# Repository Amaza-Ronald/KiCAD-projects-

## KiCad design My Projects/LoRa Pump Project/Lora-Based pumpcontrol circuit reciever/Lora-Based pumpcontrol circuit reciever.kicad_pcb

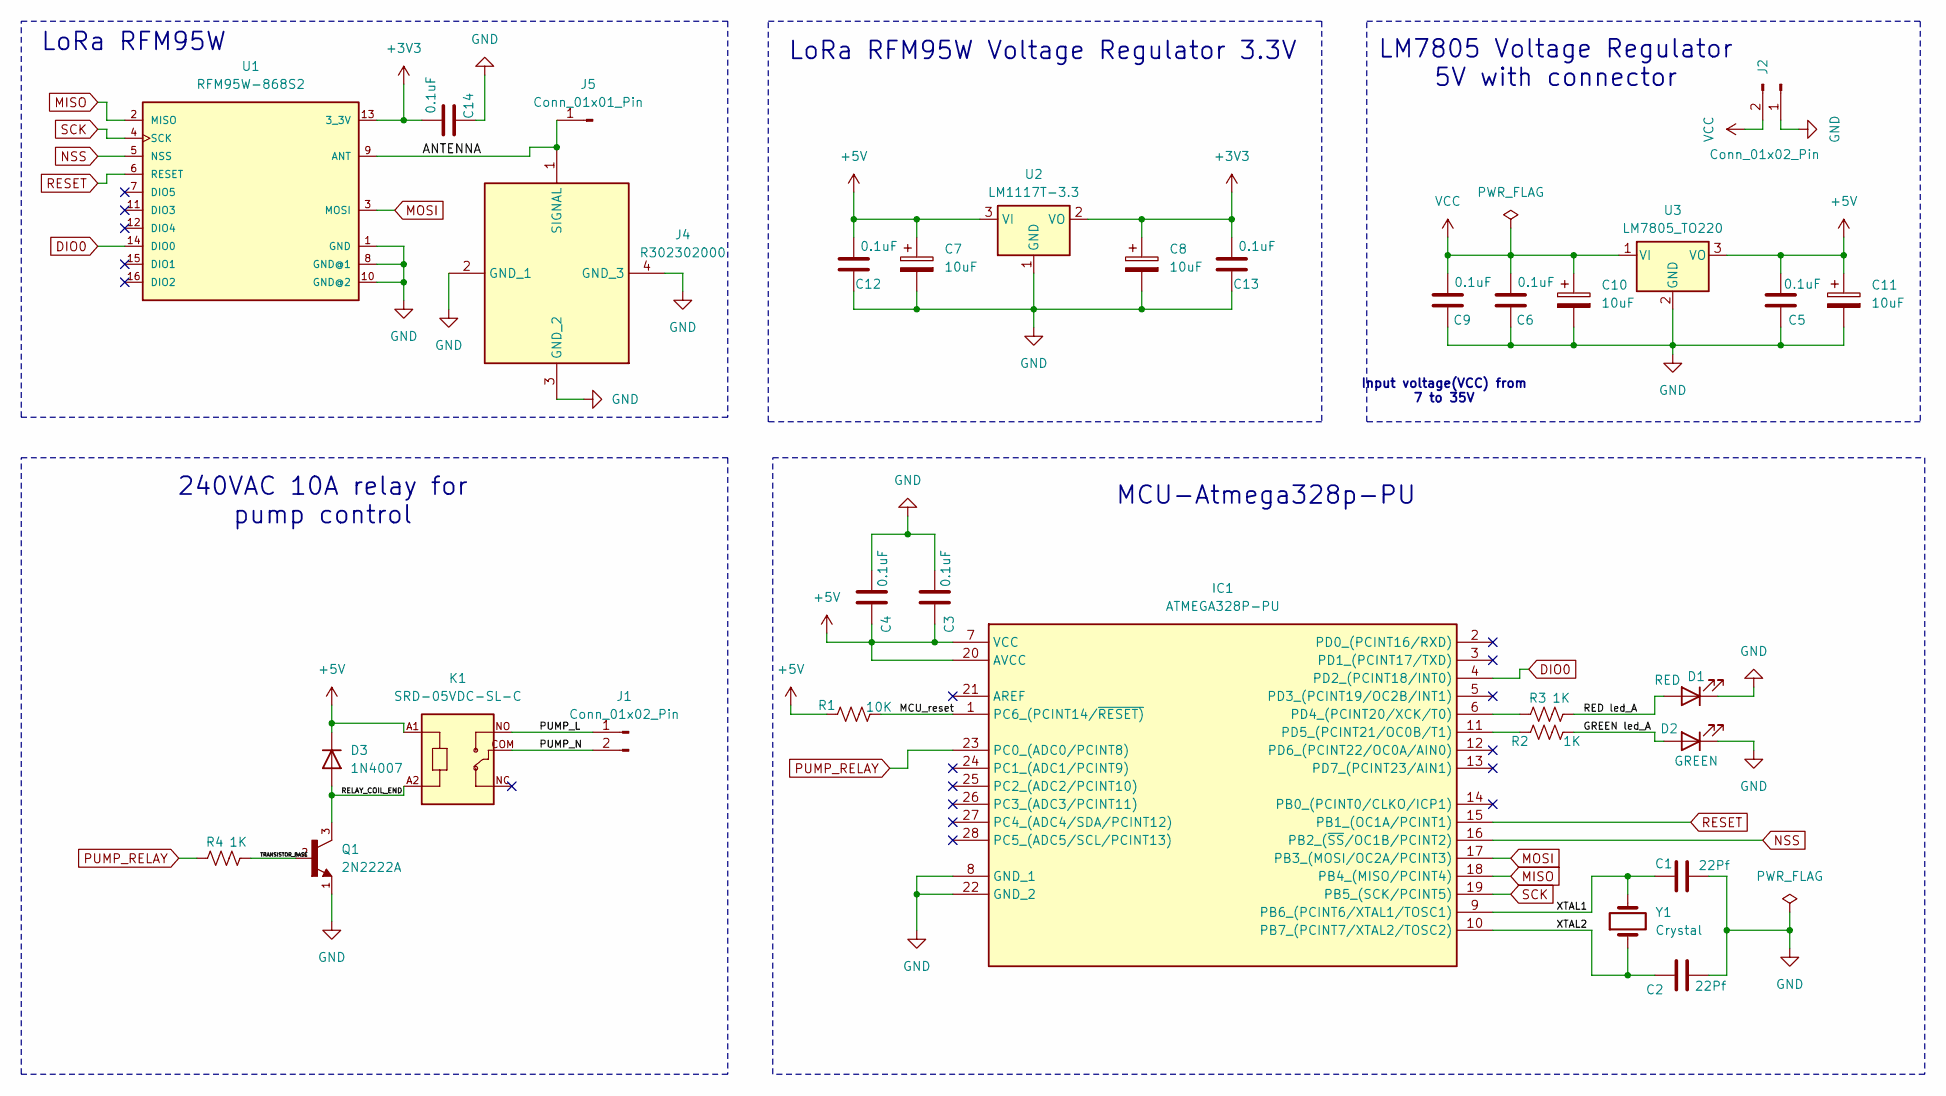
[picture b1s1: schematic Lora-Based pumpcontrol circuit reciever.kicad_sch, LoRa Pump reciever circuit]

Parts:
C1, C2: 22Pf; C_Disc_D3.0mm_W1.6mm_P2.50mm
C3, C4, C5, C6, C9, C12, C13, C14: 0.1uF; C_Disc_D4.3mm_W1.9mm_P5.00mm
C7, C8, C10, C11: 10uF; CP_Radial_D4.0mm_P1.50mm
D1: RED; LED_D3.0mm
D2: GREEN; LED_D3.0mm
D3: 1N4007; D_DO-41_SOD81_P10.16mm_Horizontal
IC1: ATMEGA328P-PU; DIP794W53P254L3467H457Q28N; Manufacturer_Part_Number ATMEGA328P-PU
J1, J2: Conn_01x02_Pin; PhoenixContact_MCV_1,5_2-G-5.08_1x02_P5.08mm_Vertical
J4: R302302000; Mouser Part Number 501-R302302000
J5: Conn_01x01_Pin; PinHeader_1x01_P2.54mm_Vertical
K1: SRD-05VDC-SL-C; RELAY_SRD-05VDC-SL-C
Q1: 2N2222A; TO92254P470H750-3; PARTREV N/A; DigiKey_Part_Number 5245-2N2222A-ND
R1: 10K; R_Axial_DIN0204_L3.6mm_D1.6mm_P5.08mm_Horizontal
R2, R3, R4: 1K; R_Axial_DIN0204_L3.6mm_D1.6mm_P5.08mm_Horizontal
U1: RFM95W-868S2; XCVR_RFM95W-868S2
U2: LM1117T-3.3; TO-220-3_Horizontal_TabDown
U3: LM7805_TO220; TO-220-3_Horizontal_TabDown
Y1: Crystal; Crystal_HC49-4H_Vertical

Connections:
+3V3: C8.1, C13.2, C14.2, U1.13 (3_3V), U2.2 (VO)
+5V: C3.1, C4.1, C5.2, C7.1, C11.1, C12.2, D3.1 (K), IC1.7 (VCC), IC1.20 (AVCC), K1.A1, R1.1, U2.3 (VI), U3.3 (VO)
/ANTENNA: J4.1 (SIGNAL), J5.1, U1.9 (ANT)
/GREEN led_A: D2.2 (A), R2.2
/MCU_reset: IC1.1 (PC6_(PCINT14/~RESET)), R1.2
/PUMP_L: J1.1, K1.NO
/PUMP_N: J1.2, K1.COM
/RED led_A: D1.2 (A), R3.2
/RELAY_COIL_END: D3.2 (A), K1.A2, Q1.3
/TRANSISTOR_BASE: Q1.2, R4.2
/XTAL1: C1.1, IC1.9 (PB6_(PCINT6/XTAL1/TOSC1)), Y1.2
/XTAL2: C2.1, IC1.10 (PB7_(PCINT7/XTAL2/TOSC2)), Y1.1
DIO0: IC1.4 (PD2_(PCINT18/INT0)), U1.14 (DIO0)
GND: C1.2, C2.2, C3.2, C4.2, C5.1, C6.1, C7.2, C8.2, C9.1, C10.2, C11.2, C12.1, C13.1, C14.1, D1.1 (K), D2.1 (K), IC1.8 (GND_1), IC1.22 (GND_2), J2.1, J4.2 (GND_1), J4.3 (GND_2), J4.4 (GND_3), Q1.1, U1.1 (GND), U1.8 (GND@1), U1.10 (GND@2), U2.1 (GND), U3.2 (GND)
MISO: IC1.18 (PB4_(MISO/PCINT4)), U1.2 (MISO)
MOSI: IC1.17 (PB3_(MOSI/OC2A/PCINT3)), U1.3 (MOSI)
NSS: IC1.16 (PB2_(~SS/OC1B/PCINT2)), U1.5 (NSS)
unnamed: IC1.6 (PD4_(PCINT20/XCK/T0)), R3.1
unnamed: IC1.11 (PD5_(PCINT21/OC0B/T1)), R2.1
PUMP_RELAY: IC1.23 (PC0_(ADC0/PCINT8)), R4.1
RESET: IC1.15 (PB1_(OC1A/PCINT1)), U1.6 (RESET)
SCK: IC1.19 (PB5_(SCK/PCINT5)), U1.4 (SCK)
VCC: C6.2, C9.2, C10.1, J2.2, U3.1 (VI)

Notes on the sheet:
LoRa RFM95W Voltage Regulator 3.3V
LM7805 Voltage Regulator 5V with connector
Input voltage(VCC) from 7 to 35V
LoRa RFM95W
MCU-Atmega328p-PU
240VAC 10A relay for pump control

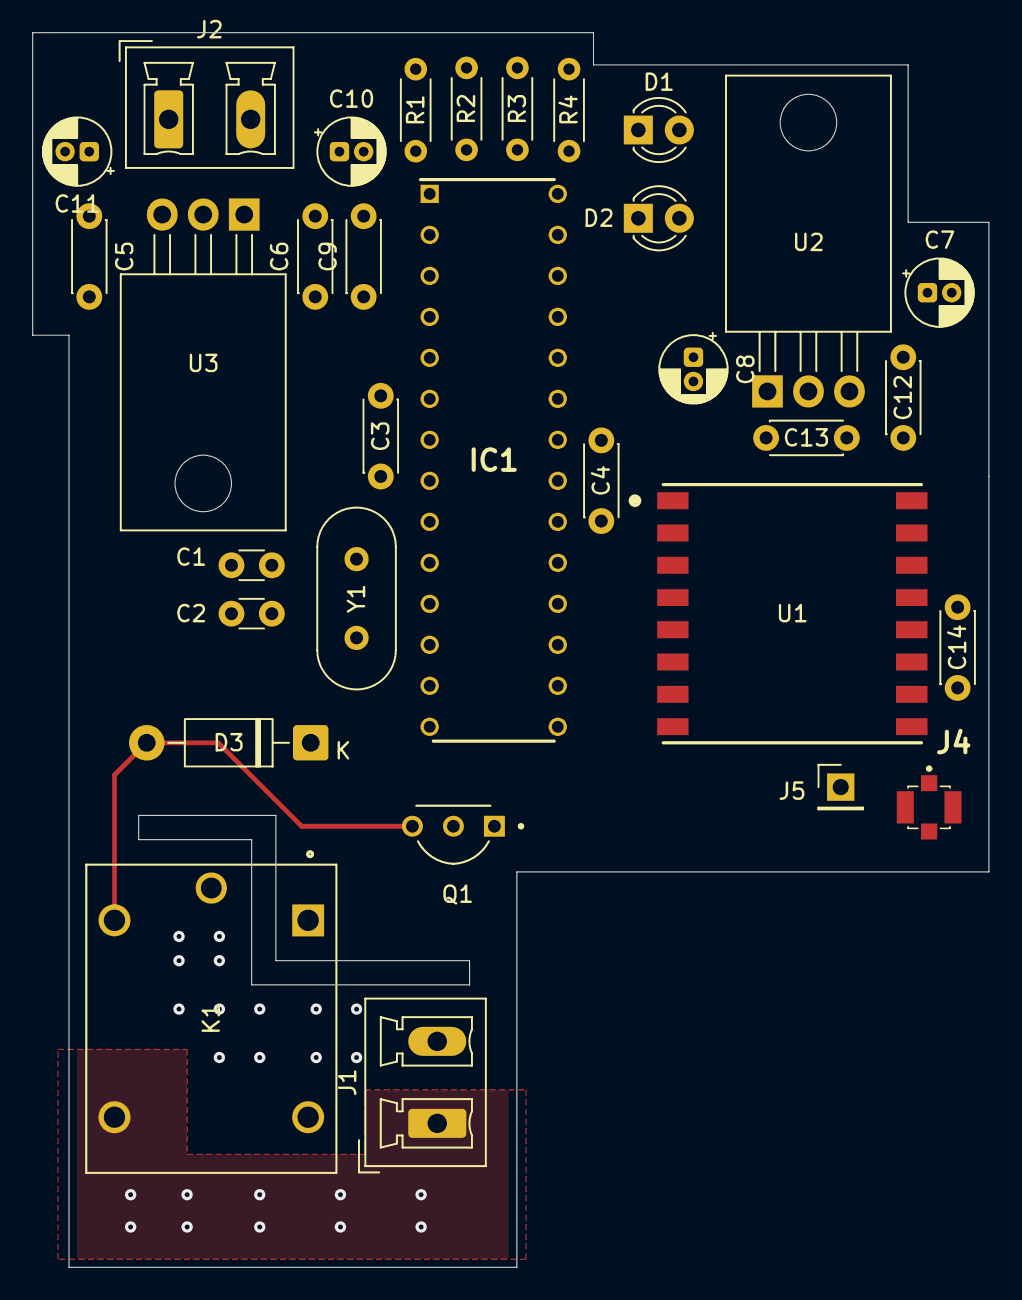
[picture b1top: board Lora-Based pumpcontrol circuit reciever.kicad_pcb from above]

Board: 2 copper layers, 59.2 x 76.5 mm, 32 parts (0 on the bottom side), 23 nets.

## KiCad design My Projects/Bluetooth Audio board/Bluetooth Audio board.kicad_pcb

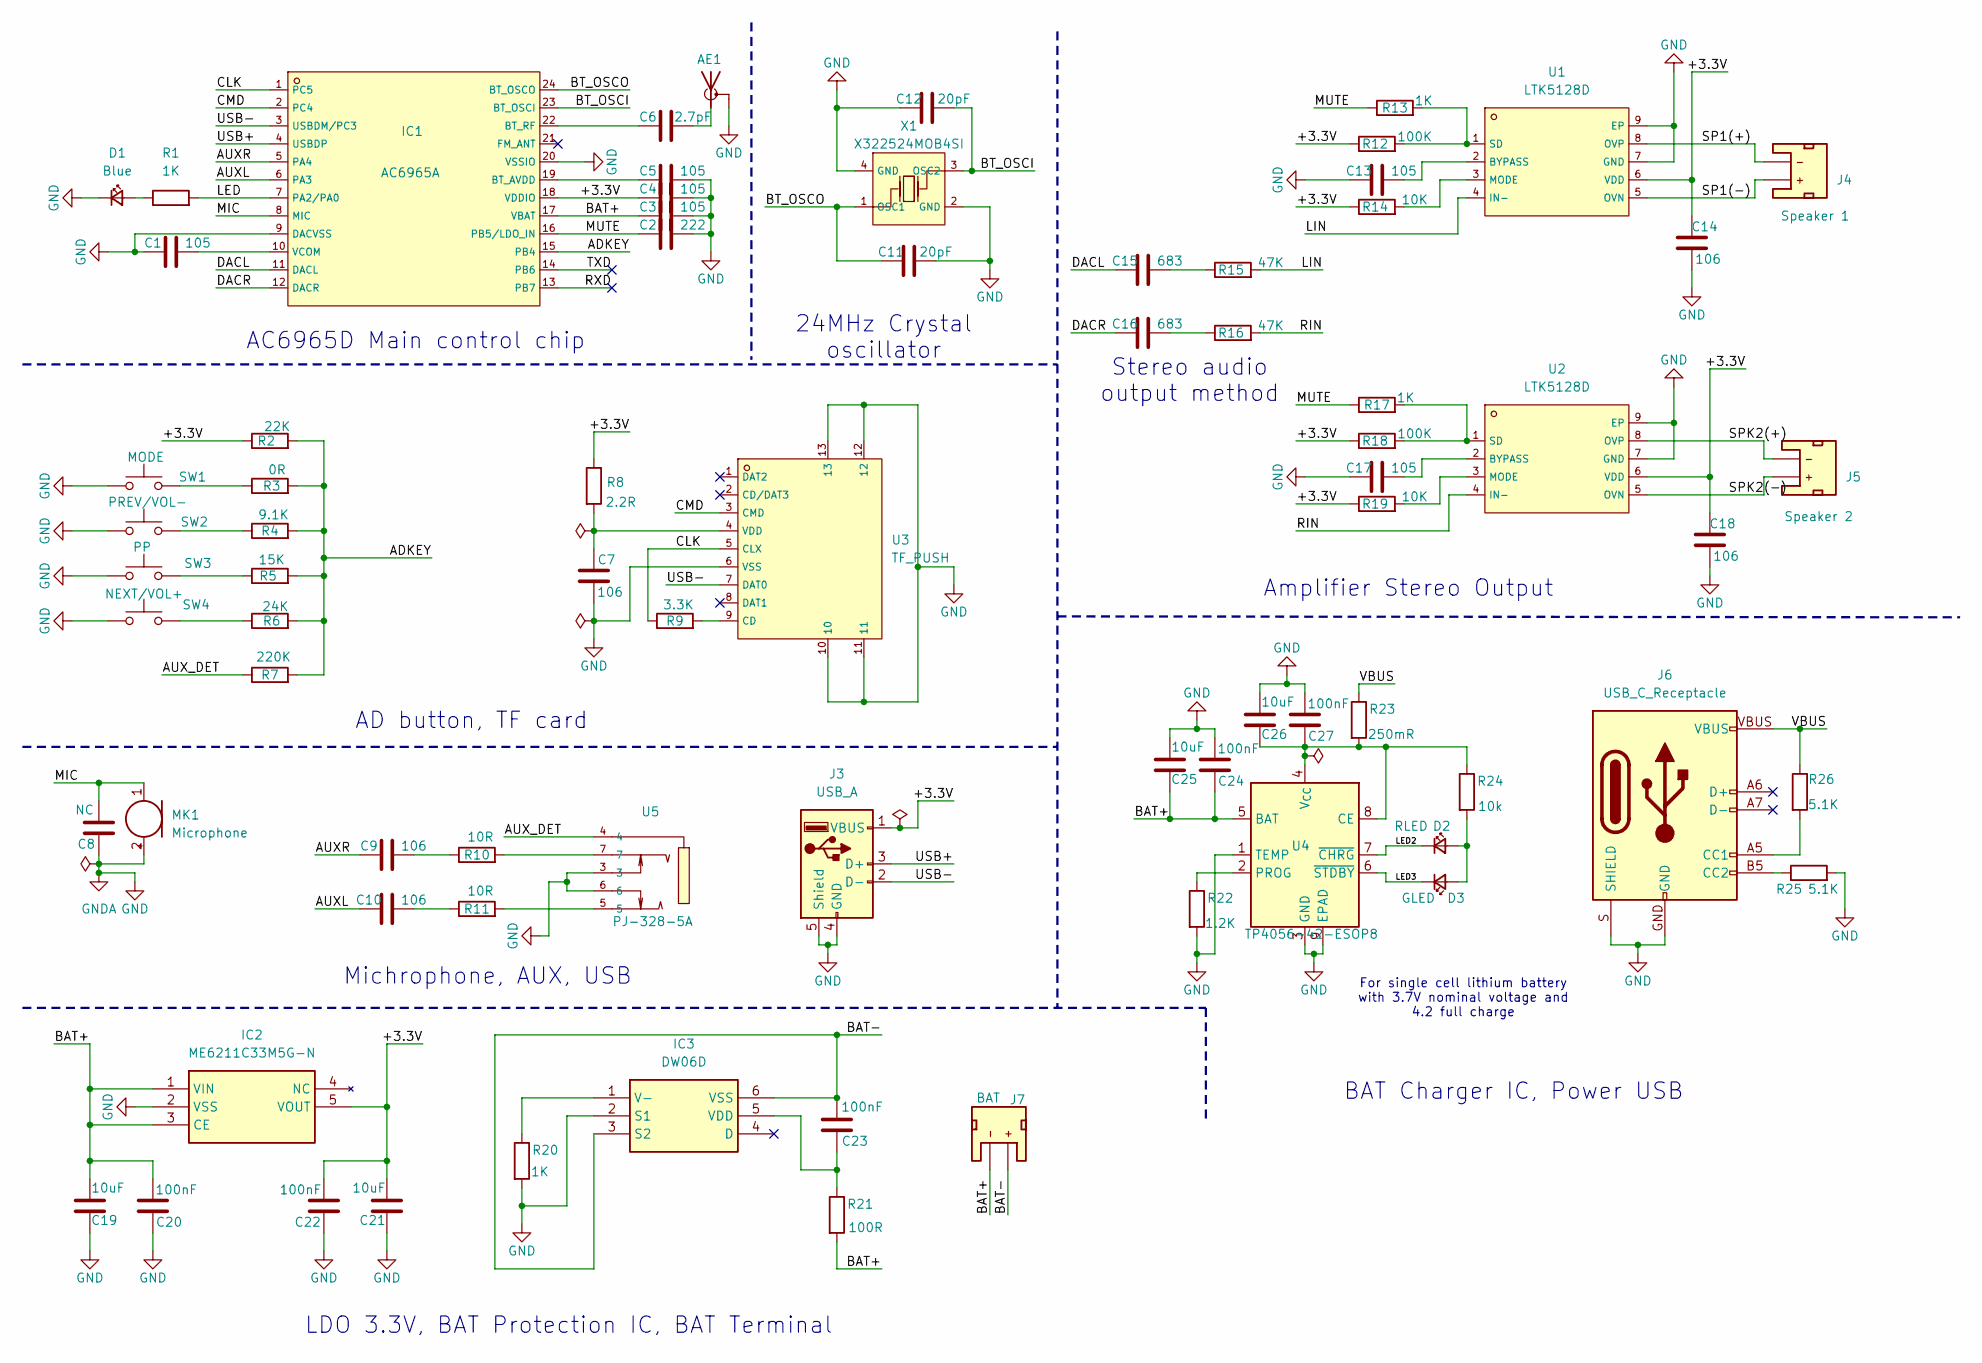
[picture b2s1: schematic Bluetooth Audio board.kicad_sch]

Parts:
AE1: Antenna; Texas_SWRA117D_2.4GHz_Left
C1, C3, C4, C5, C13, C17: 105; C_0603_1608Metric
C2: 222; C_0603_1608Metric
C6: 2.7pF; C_0603_1608Metric
C7, C9, C10, C14, C18: 106; C_0603_1608Metric
C8: NC; C_0603_1608Metric
C11, C12: 20pF; C_0603_1608Metric
C15, C16: 683; C_0603_1608Metric
C19, C21, C25, C26: 10uF; C_0603_1608Metric
C20, C22, C23, C24, C27: 100nF; C_0603_1608Metric
D1: Blue; LED_0603_1608Metric_Blue
D2: RLED; LED_0603_1608Metric_Red
D3: GLED; LED_0603_1608Metric_Green
IC1: AC6965A; QSOP-24_L8.7-W3.9-P0.64-LS6.0-BL; LCSC C46656375
IC2: ME6211C33M5G-N; SOT95P270X145-5N; Manufacturer_Part_Number ME6211C33M5G-N
IC3: DW06D; SOT95P290X124-6N; Manufacturer_Part_Number DW06D
J3: USB_A; USB_A_Molex_67643_Horizontal
J4: Speaker 1; JST_1x02_P2.0mm_Horizontal_SMD
J5: Speaker 2; JST_1x02_P2.0mm_Horizontal_SMD
J6: USB_C_Receptacle; USB-C_16
J7: BAT; JST_1x02_P2.0mm_Horizontal_SMD
MK1: Microphone; MIC-TH_BD6.0-P1.90-D0.4-L
R1, R13, R17, R20: 1K; R_0603_1608Metric
R2: 22K; R_0603_1608Metric
R3: 0R; R_0603_1608Metric
R4: 9.1K; R_0603_1608Metric
R5: 15K; R_0603_1608Metric
R6: 24K; R_0603_1608Metric
R7: 220K; R_0603_1608Metric
R8: 2.2R; R_0603_1608Metric
R9: 3.3K; R_0603_1608Metric
R10, R11: 10R; R_0603_1608Metric
R12, R18: 100K; R_0603_1608Metric
R14, R19: 10K; R_0603_1608Metric
R15, R16: 47K; R_0603_1608Metric
R21: 100R; R_0603_1608Metric
R22: 1.2K; R_0603_1608Metric
R23: 250mR; R_0603_1608Metric
R24: 10k; R_0603_1608Metric
R25, R26: 5.1K; R_0603_1608Metric
SW1: MODE; Push_SMD_6x3.5mm; Mfg Part# 8-004 SMD Button 8x3.6mm Height=2.5mm
SW2: PREV/VOL-; Push_SMD_6x3.5mm; Mfg Part# 8-004 SMD Button 8x3.6mm Height=2.5mm
SW3: PP; Push_SMD_6x3.5mm; Mfg Part# 8-004 SMD Button 8x3.6mm Height=2.5mm
SW4: NEXT/VOL+; Push_SMD_6x3.5mm; Mfg Part# 8-004 SMD Button 8x3.6mm Height=2.5mm
U1, U2: LTK5128D; ESOP-8_L4.9-W3.9-P1.27-LS6.0-BL-EP; LCSC C406244
U3: TF_PUSH; TF-SMD_TF-PUSH; LCSC C393941
U4: TP4056-42-ESOP8; ESOP-8_L4.9-W3.9-P1.27-LS6.0-BL-EP
U5: PJ-328-5A; AUDIO-SMD_PJ-328-5A; LCSC C707231
X1: X322524MOB4SI; CRYSTAL-SMD_4P-L3.2-W2.5-BL; LCSC C70590

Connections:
/+3.3V: C4.1, C14.1, C18.1, C21.2, C22.2, IC1.18 (VDDIO), IC2.5 (VOUT), J3.1 (VBUS), R2.1, R8.1, R12.1, R14.1, R18.1, R19.1, U1.6 (VDD), U2.6 (VDD)
/ADKEY: IC1.15 (PB4), R2.2, R3.2, R4.2, R5.2, R6.2, R7.2
/AUXL: C10.1, IC1.6 (PA3)
/AUXR: C9.1, IC1.5 (PA4)
/AUX_DET: R7.1, U5.4
/BAT+: C3.1, C19.2, C20.2, C24.1, C25.1, IC1.17 (VBAT), IC2.1 (VIN), IC2.3 (CE), J7.1 (-), R21.2, U4.5 (BAT)
/BAT-: C23.2, IC3.3 (S2), IC3.6 (VSS), J7.2 (+)
/BT_OSCI: C12.2, IC1.23 (BT_OSCI), X1.3 (OSC2)
/BT_OSCO: C11.1, IC1.24 (BT_OSCO), X1.1 (OSC1)
/CLK: IC1.1 (PC5), R9.1, U3.5 (CLX)
/CMD: IC1.2 (PC4), U3.3 (CMD)
/DACL: C15.1, IC1.11 (DACL)
/DACR: C16.1, IC1.12 (DACR)
/LED: IC1.7 (PA2/PA0), R1.2
/LED2: D2.1 (K), U4.7 (~CHRG)
/LED3: D3.1 (K), U4.6 (~STDBY)
/LIN: R15.2, U1.4 (IN-)
/MIC: C8.2, IC1.8 (MIC), MK1.1 (-)
/MUTE: C2.1, IC1.16 (PB5/LDO_IN), R13.1, R17.1
/RIN: R16.2, U2.4 (IN-)
/RXD: IC1.13 (PB7)
/SP1(+): J4.1 (-), U1.8 (OVP)
/SP1(-): J4.2 (+), U1.5 (OVN)
/SPK2(+): J5.1 (-), U2.8 (OVP)
/SPK2(-): J5.2 (+), U2.5 (OVN)
/TXD: IC1.14 (PB6)
/USB+: IC1.4 (USBDP), J3.3 (D+)
/USB-: IC1.3 (USBDM/PC3), J3.2 (D-), U3.7 (DAT0)
/VBUS: J6.VBUS, R23.1, R26.1
GND: AE1.2 (GND), C1.1, C2.2, C3.2, C4.2, C5.2, C7.2, C8.1, C11.2, C12.1, C13.1, C14.2, C17.1, C18.2, C19.1, C20.1, C21.1, C22.1, C24.2, C25.2, C26.2, C27.2, D1.1 (K), IC1.9 (DACVSS), IC1.20 (VSSIO), IC2.2 (VSS), IC3.2 (S1), J3.4 (GND), J3.5 (Shield), J6.GND, J6.S (SHIELD), MK1.2 (+), R20.2, R22.2, R25.2, SW1.1, SW2.1, SW3.1, SW4.1, U1.7 (GND), U1.9 (EP), U2.7 (GND), U2.9 (EP), U3.6 (VSS), U3.10, U3.11, U3.12, U3.13, U4.1 (TEMP), U4.3 (GND), U4.9 (EPAD), U5.3, U5.6, X1.2 (GND), X1.4 (GND)
unnamed: AE1.1 (A), C6.2
unnamed: C9.2, R10.1
unnamed: C10.2, R11.1
unnamed: C15.2, R15.1
unnamed: C16.2, R16.1
unnamed: D1.2 (A), R1.1
unnamed: D2.2 (A), D3.2 (A), R24.2
unnamed: C5.1, IC1.19 (BT_AVDD)
unnamed: C6.1, IC1.22 (BT_RF)
unnamed: C1.2, IC1.10 (VCOM)
unnamed: IC3.1 (V-), R20.1
unnamed: C23.1, IC3.5 (VDD), R21.1
unnamed: J6.A5 (CC1), R26.2
unnamed: J6.B5 (CC2), R25.1
unnamed: R3.1, SW1.2
unnamed: R4.1, SW2.2
unnamed: R5.1, SW3.2
unnamed: R6.1, SW4.2
unnamed: R10.2, U5.7
unnamed: R11.2, U5.5
unnamed: C13.2, U1.2 (BYPASS)
unnamed: R14.2, U1.3 (MODE)
unnamed: R12.2, R13.2, U1.1 (SD)
unnamed: C17.2, U2.2 (BYPASS)
unnamed: R19.2, U2.3 (MODE)
unnamed: R17.2, R18.2, U2.1 (SD)
unnamed: R9.2, U3.9 (CD)
unnamed: C7.1, R8.2, U3.4 (VDD)
unnamed: C26.1, C27.1, R23.2, R24.1, U4.4 (V_{CC}), U4.8 (CE)
unnamed: R22.1, U4.2 (PROG)

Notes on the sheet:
AC6965D Main control chip
For single cell lithium battery with 3.7V nominal voltage and 4.2 full charge
BAT Charger IC, Power USB
Stereo audio output method
Michrophone, AUX, USB
AD button, TF card
Amplifier Stereo Output
24MHz Crystal oscillator
LDO 3.3V, BAT Protection IC, BAT Terminal

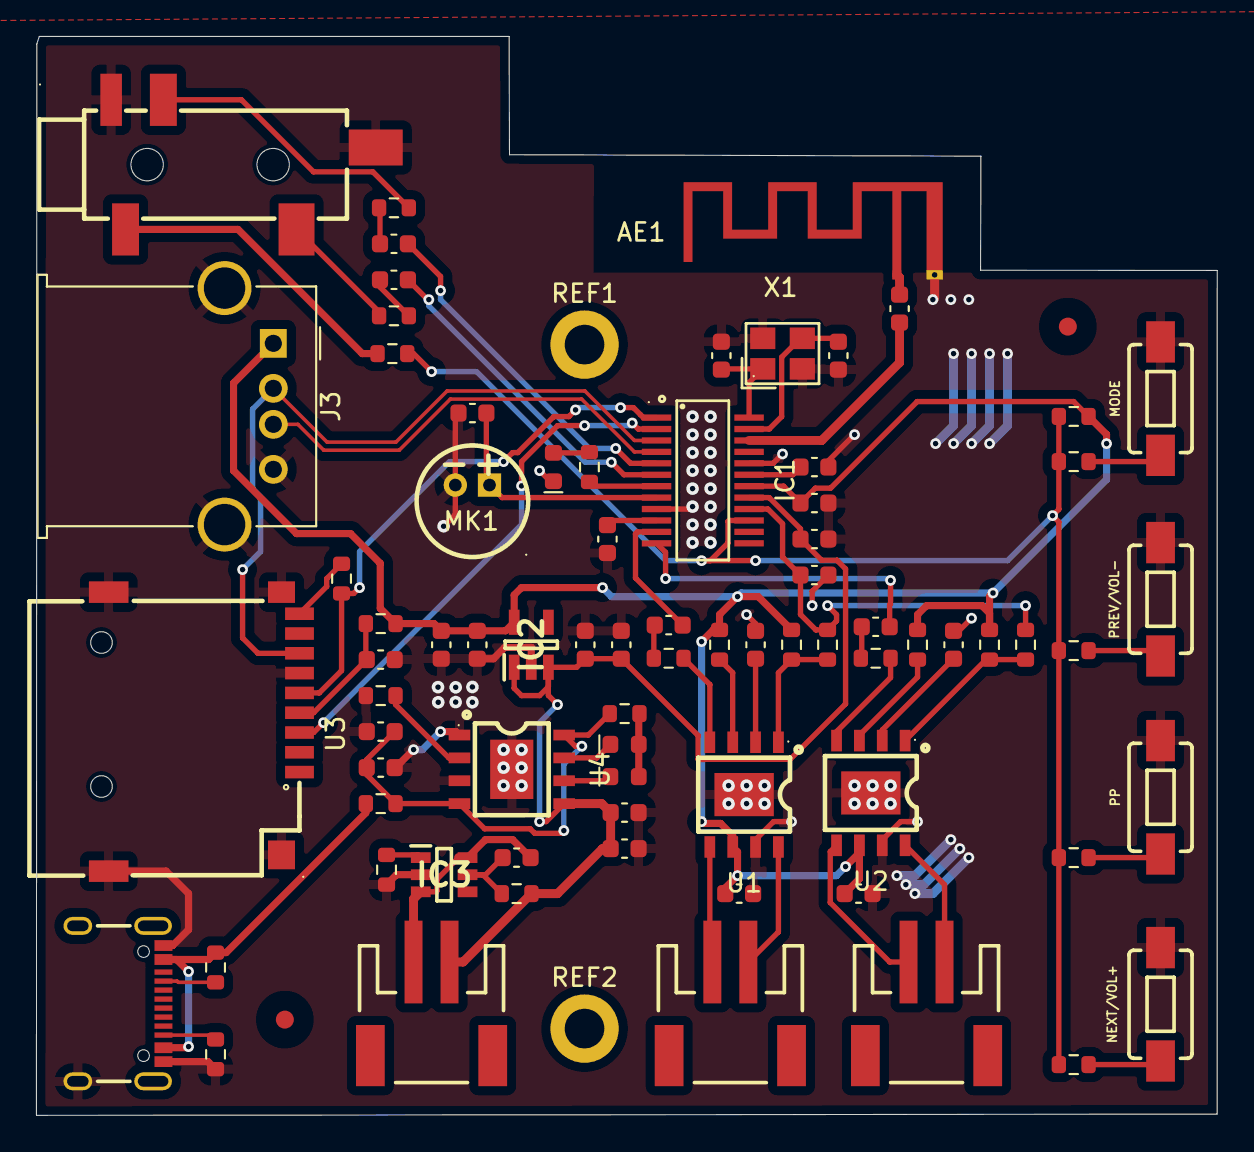
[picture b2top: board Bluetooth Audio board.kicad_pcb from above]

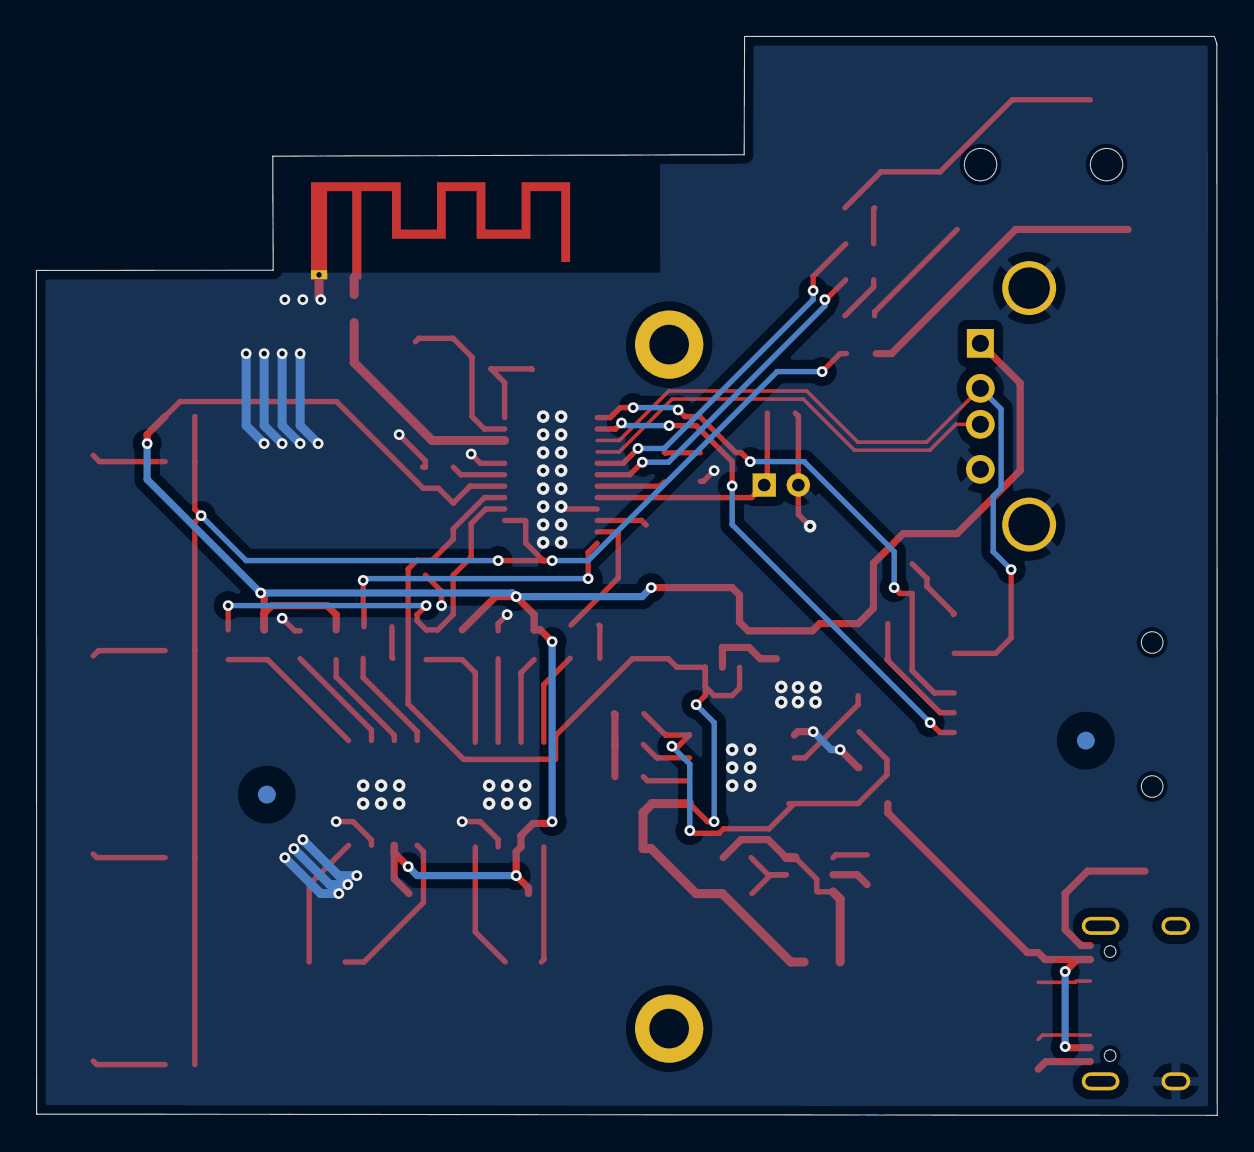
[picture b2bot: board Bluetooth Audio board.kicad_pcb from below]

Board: 2 copper layers, 65.6 x 59.9 mm, 82 parts (2 on the bottom side), 58 nets.

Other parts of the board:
REF1, REF2#2, REF3, REF4: Fiducial_1mm_Mask3mm
REF1#2, REF2: MountingHole_2.2mm_M2_DIN965_Pad

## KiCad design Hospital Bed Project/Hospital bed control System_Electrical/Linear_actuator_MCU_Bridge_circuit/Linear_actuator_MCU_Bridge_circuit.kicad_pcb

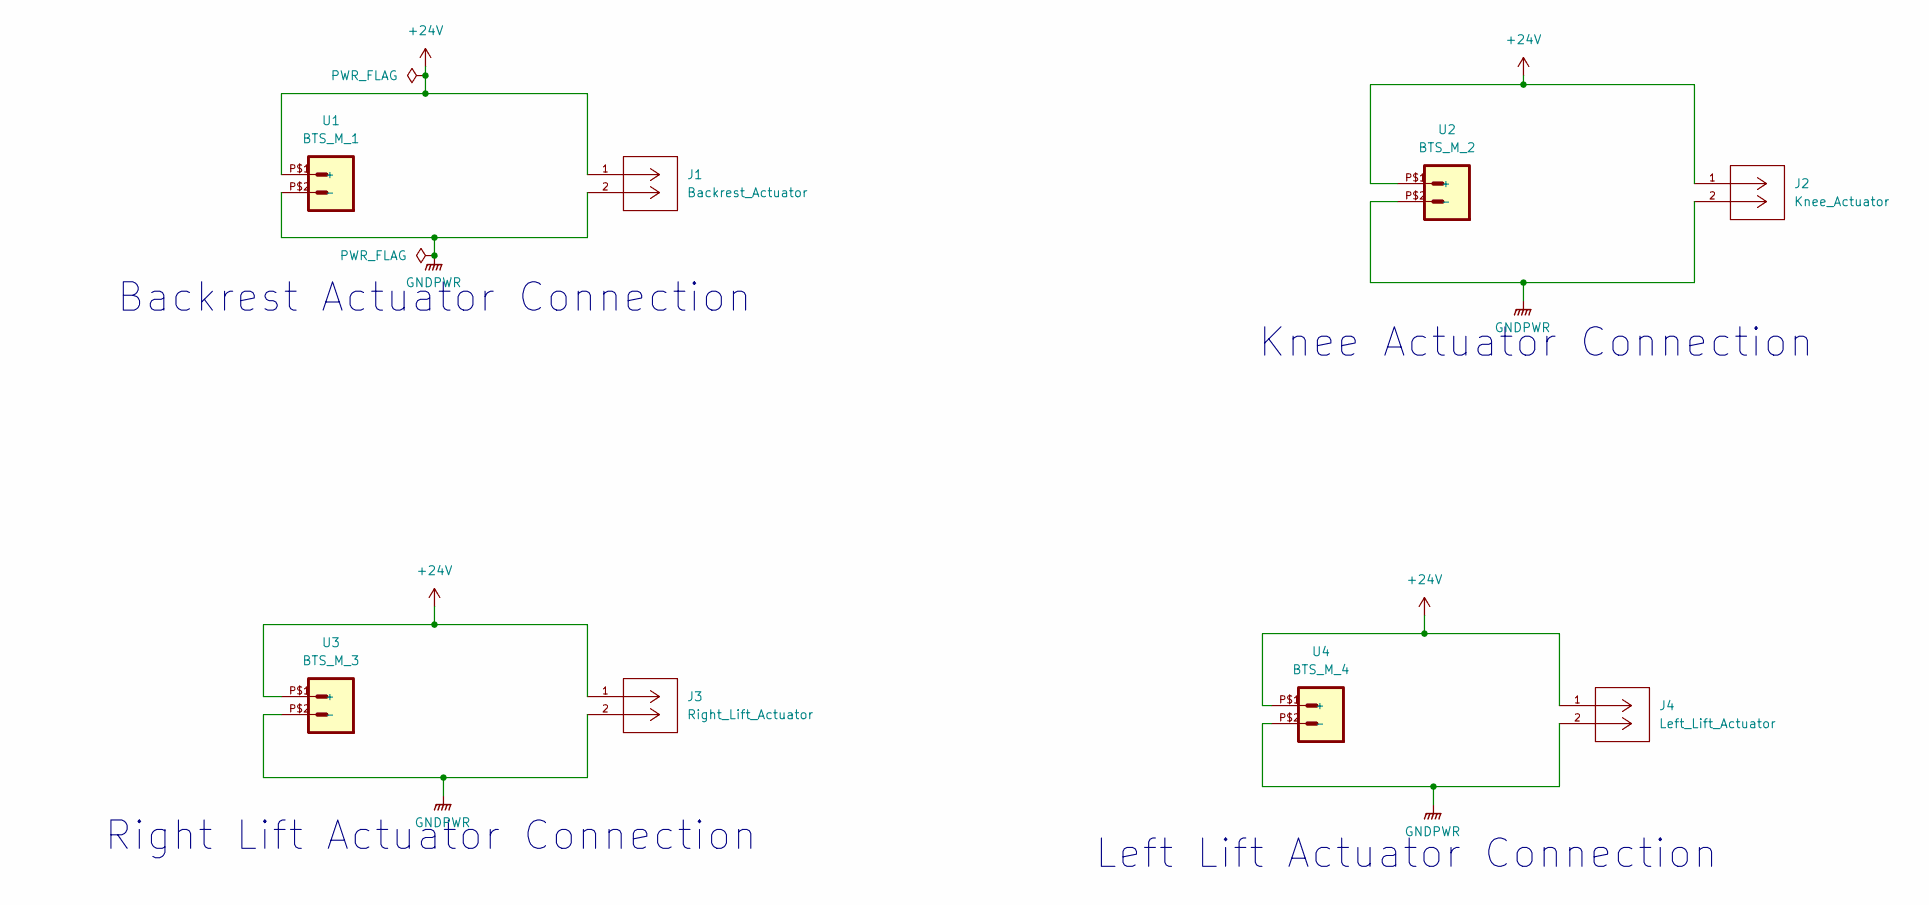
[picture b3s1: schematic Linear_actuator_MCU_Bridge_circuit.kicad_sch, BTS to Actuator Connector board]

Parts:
J1: Backrest_Actuator; CONN_395224002_MOL; MANUFACTURER_PART_NUMBER 395224002
J2: Knee_Actuator; CONN_395224002_MOL; MANUFACTURER_PART_NUMBER 395224002
J3: Right_Lift_Actuator; CONN_395224002_MOL; MANUFACTURER_PART_NUMBER 395224002
J4: Left_Lift_Actuator; CONN_395224002_MOL; MANUFACTURER_PART_NUMBER 395224002
U1: BTS_M_1; XT30UPB-M
U2: BTS_M_2; XT30UPB-M
U3: BTS_M_3; XT30UPB-M
U4: BTS_M_4; XT30UPB-M

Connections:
+24V: J1.1, J2.1, J3.1, J4.1, U1.P$1 (+), U2.P$1 (+), U3.P$1 (+), U4.P$1 (+)
GNDPWR: J1.2, J2.2, J3.2, J4.2, U1.P$2 (-), U2.P$2 (-), U3.P$2 (-), U4.P$2 (-)

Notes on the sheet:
Right Lift Actuator Connection
Backrest Actuator Connection
Left Lift Actuator Connection
Knee Actuator Connection

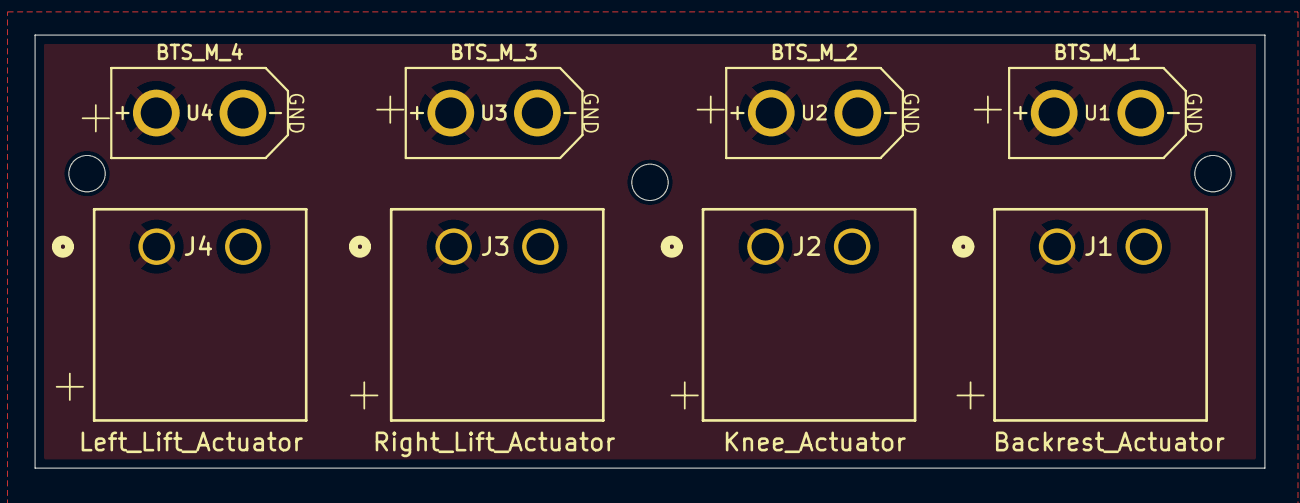
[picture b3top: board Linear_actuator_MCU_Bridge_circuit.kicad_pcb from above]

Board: 2 copper layers, 71.0 x 25.0 mm, 11 parts (0 on the bottom side), 2 nets.

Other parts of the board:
REF1, REF2, REF3: screw; MountingHole_2.1mm

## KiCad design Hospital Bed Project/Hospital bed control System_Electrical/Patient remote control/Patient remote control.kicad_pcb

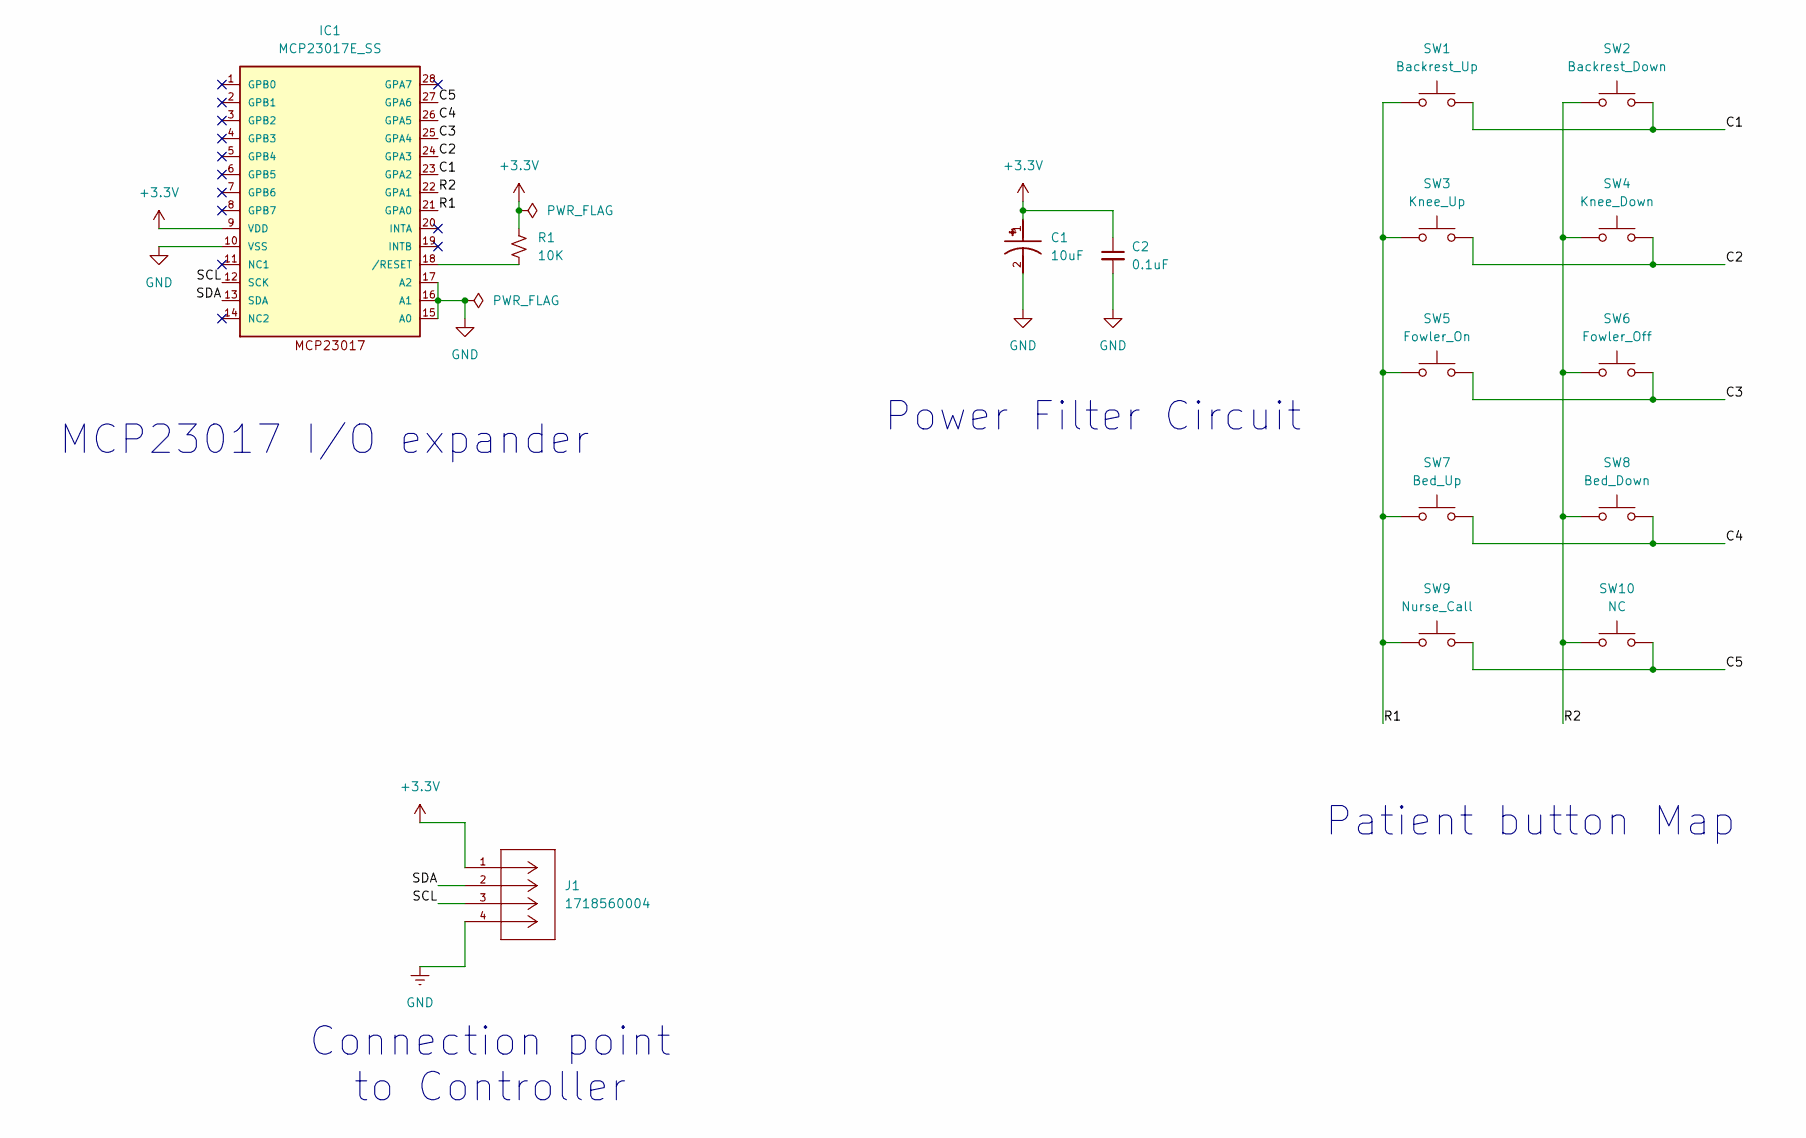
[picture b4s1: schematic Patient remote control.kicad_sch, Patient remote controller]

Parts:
C1: 10uF; CAP_EEFSX0D221ER; PARTREV 1-Oct-19
C2: 0.1uF; C_1206_3216Metric_Pad1.33x1.80mm_HandSolder
IC1: MCP23017E_SS; SSOP28
J1: 1718560004; CONN04_1718560004_MOL; MANUFACTURER_PART_NUMBER 1718560004
R1: 10K; R_0603_1608Metric
SW1: Backrest_Up; SW_PUSH_6mm
SW2: Backrest_Down; SW_PUSH_6mm
SW3: Knee_Up; SW_PUSH_6mm
SW4: Knee_Down; SW_PUSH_6mm
SW5: Fowler_On; SW_PUSH_6mm
SW6: Fowler_Off; SW_PUSH_6mm
SW7: Bed_Up; SW_PUSH_6mm
SW8: Bed_Down; SW_PUSH_6mm
SW9: Nurse_Call; SW_PUSH_6mm
SW10: NC; SW_PUSH_6mm

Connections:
+3.3V: C1.1, C2.1, IC1.9 (VDD), J1.1, R1.1
/C1: IC1.23 (GPA2), SW1.2, SW2.2
/C2: IC1.24 (GPA3), SW3.2, SW4.2
/C3: IC1.25 (GPA4), SW5.2, SW6.2
/C4: IC1.26 (GPA5), SW7.2, SW8.2
/C5: IC1.27 (GPA6), SW9.2, SW10.2
/R1: IC1.21 (GPA0), SW1.1, SW3.1, SW5.1, SW7.1, SW9.1
/R2: IC1.22 (GPA1), SW2.1, SW4.1, SW6.1, SW8.1, SW10.1
/SCL: IC1.12 (SCK), J1.3
/SDA: IC1.13 (SDA), J1.2
GND: C1.2, C2.2, IC1.10 (VSS), IC1.15 (A0), IC1.16 (A1), IC1.17 (A2), J1.4
unnamed: IC1.18 (/RESET), R1.2

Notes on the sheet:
MCP23017 I/O expander
Connection point to Controller
Power Filter Circuit
Patient button Map

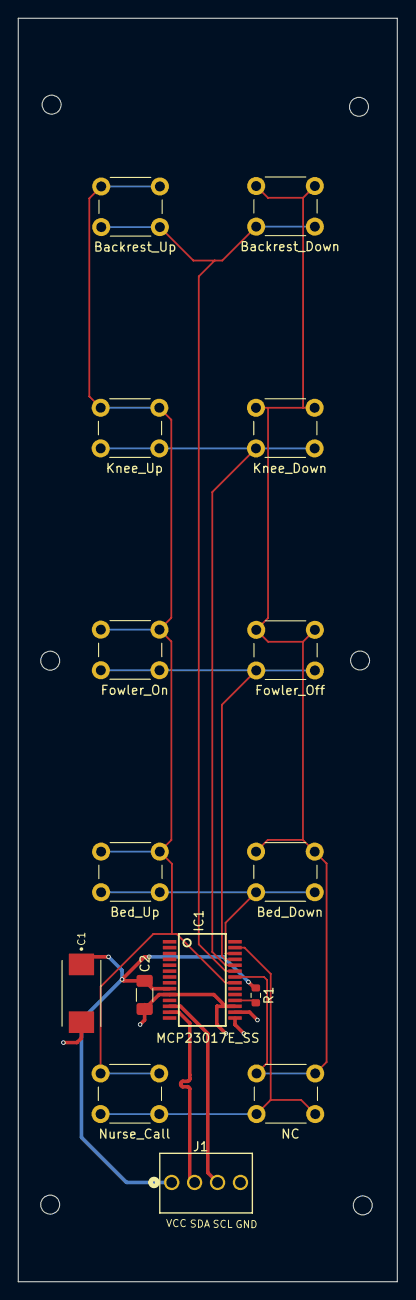
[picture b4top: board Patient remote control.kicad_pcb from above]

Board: 2 copper layers, 42.0 x 140.0 mm, 21 parts (0 on the bottom side), 12 nets.

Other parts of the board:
REF1, REF2, REF3, REF4, REF5, REF6: MountingHole_2.1mm

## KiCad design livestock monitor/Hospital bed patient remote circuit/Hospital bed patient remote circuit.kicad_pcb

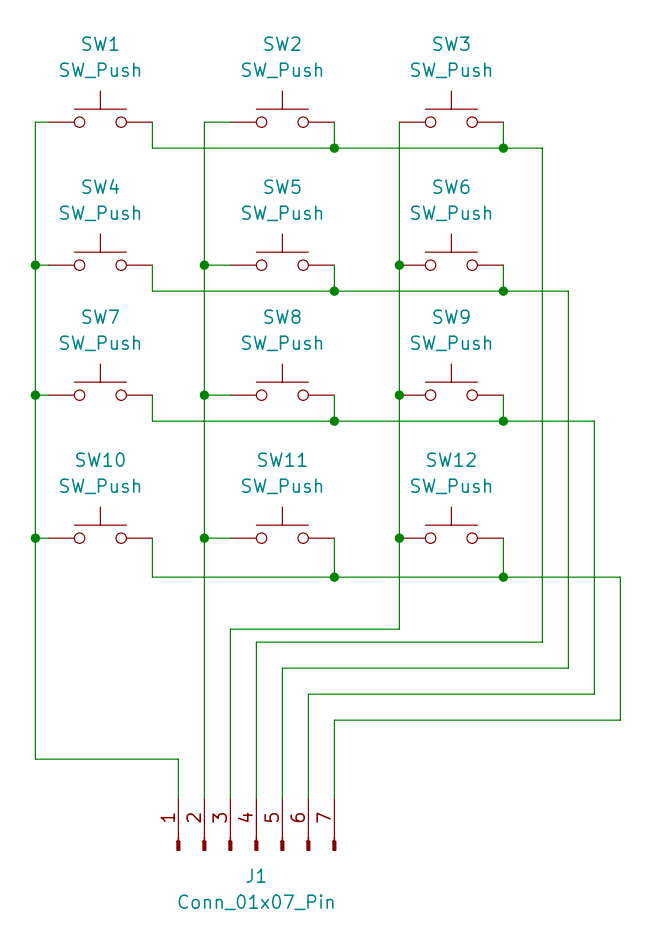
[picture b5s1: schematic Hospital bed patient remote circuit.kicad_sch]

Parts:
J1: Conn_01x07_Pin; PinHeader_1x07_P2.54mm_Vertical
SW1, SW2, SW3, SW4, SW5, SW6, SW7, SW8, SW9, SW10, SW11, SW12: SW_Push; SW_PUSH_6mm

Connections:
unnamed: J1.1, SW1.1, SW4.1, SW7.1, SW10.1
unnamed: J1.2, SW2.1, SW5.1, SW8.1, SW11.1
unnamed: J1.3, SW3.1, SW6.1, SW9.1, SW12.1
unnamed: J1.4, SW1.2, SW2.2, SW3.2
unnamed: J1.5, SW4.2, SW5.2, SW6.2
unnamed: J1.6, SW7.2, SW8.2, SW9.2
unnamed: J1.7, SW10.2, SW11.2, SW12.2

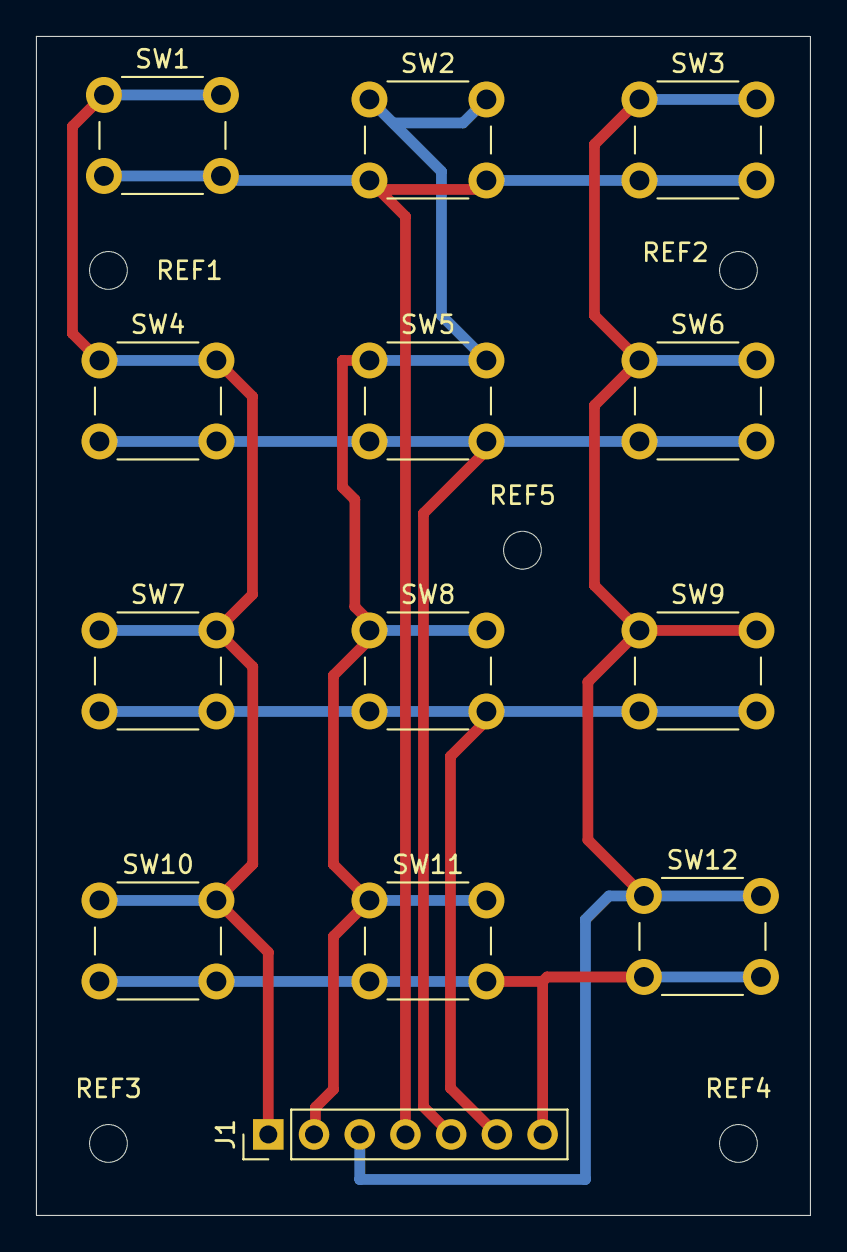
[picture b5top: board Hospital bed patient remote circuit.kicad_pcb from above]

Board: 2 copper layers, 43.0 x 65.5 mm, 18 parts (0 on the bottom side), 7 nets.

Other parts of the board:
REF1, REF2, REF3, REF4, REF5: MountingHole_2.1mm
